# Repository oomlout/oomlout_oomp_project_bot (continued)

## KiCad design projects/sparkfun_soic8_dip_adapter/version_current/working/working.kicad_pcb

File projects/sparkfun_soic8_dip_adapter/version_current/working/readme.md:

# SOIC8-DIP_Adapter by sparkfun  
This is a harvested standardized copy of a project from github.  
The original project can be found at:  
https://github.com/sparkfun/SOIC8-DIP_Adapter  
Please consult that link for additional, details, files, and license information.  
Note: It was auto harvested and if the original repo had more than one board file or anything out of the ordinary the files here are likely not representative.

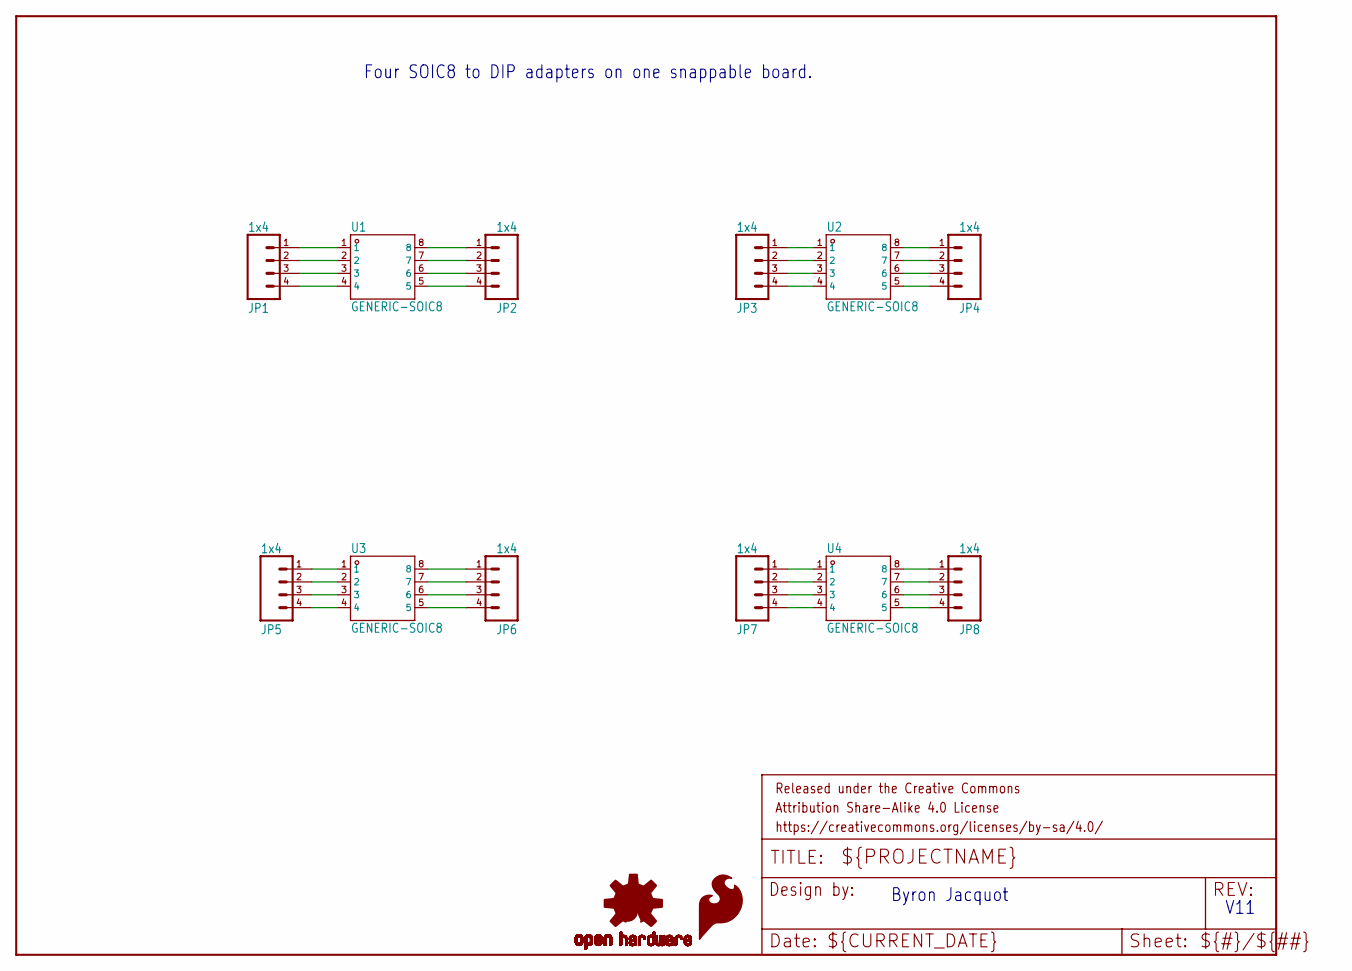
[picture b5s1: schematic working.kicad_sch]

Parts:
FRAME1: FRAME-LETTER; CREATIVE_COMMONS
JP1, JP3, JP5, JP7: 1x4; 1X04_NO_SILK
JP2, JP4, JP6, JP8: 1x4; 1X04_NO_SILK_ALL_ROUND
LOGO1: SFE_LOGO_FLAME.1_INCH; SFE_LOGO_FLAME_.1
LOGO2: OSHW-LOGOS; OSHW-LOGO-S
U1, U2, U3, U4: GENERIC-SOIC8; SO08-UNIVERSAL

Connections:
unnamed: JP1.1, U1.1
unnamed: JP1.2, U1.2
unnamed: JP1.3, U1.3
unnamed: JP1.4, U1.4
unnamed: JP2.1, U1.8
unnamed: JP2.2, U1.7
unnamed: JP2.3, U1.6
unnamed: JP2.4, U1.5
unnamed: JP3.1, U2.1
unnamed: JP3.2, U2.2
unnamed: JP3.3, U2.3
unnamed: JP3.4, U2.4
unnamed: JP4.1, U2.8
unnamed: JP4.2, U2.7
unnamed: JP4.3, U2.6
unnamed: JP4.4, U2.5
unnamed: JP5.1, U3.1
unnamed: JP5.2, U3.2
unnamed: JP5.3, U3.3
unnamed: JP5.4, U3.4
unnamed: JP6.4, U3.5
unnamed: JP6.3, U3.6
unnamed: JP6.2, U3.7
unnamed: JP6.1, U3.8
unnamed: JP7.1, U4.1
unnamed: JP7.2, U4.2
unnamed: JP7.3, U4.3
unnamed: JP7.4, U4.4
unnamed: JP8.1, U4.8
unnamed: JP8.2, U4.7
unnamed: JP8.3, U4.6
unnamed: JP8.4, U4.5

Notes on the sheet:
Four SOIC8 to DIP adapters on one snappable board.
V11
Byron Jacquot

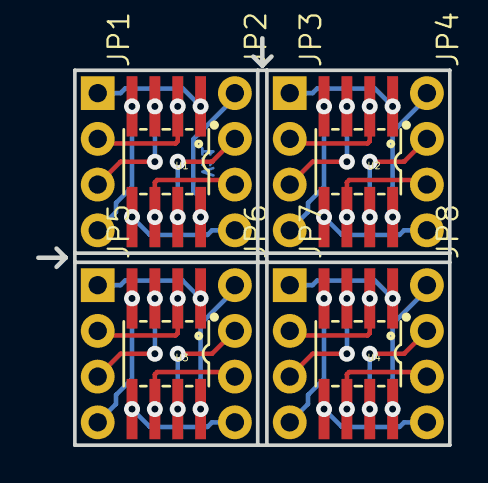
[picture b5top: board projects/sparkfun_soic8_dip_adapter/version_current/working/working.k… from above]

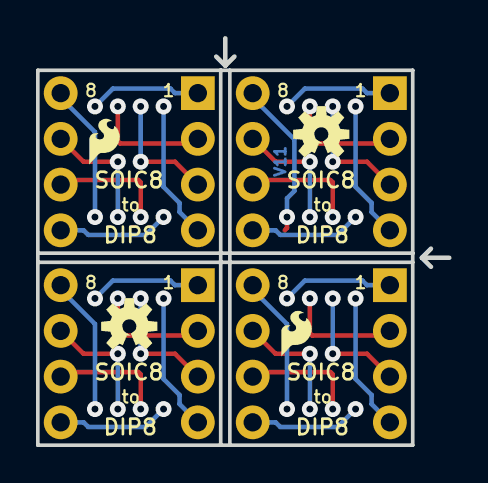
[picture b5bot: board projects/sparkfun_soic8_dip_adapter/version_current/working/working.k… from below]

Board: 2 copper layers, 22.9 x 22.6 mm, 17 parts (4 on the bottom side), 32 nets.

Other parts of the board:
LOGO3: OSHW-LOGOS; OSHW-LOGO-S
LOGO4: SFE_LOGO_FLAME.1_INCH; SFE_LOGO_FLAME_.1@1

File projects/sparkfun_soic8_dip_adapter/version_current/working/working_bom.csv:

"Id";"Designator";"Footprint";"Quantity";"Designation";"Supplier and ref";
1;"JP2,JP4,JP8,JP6";"1X04_NO_SILK_ALL_ROUND";4;"1x4";;;
2;"JP3,JP1,JP7,JP5";"1X04_NO_SILK";4;"1x4";;;
3;"U1,U3,U2,U4";"SO08-UNIVERSAL";4;"GENERIC-SOIC8";;;
4;"FRAME1";"CREATIVE_COMMONS";1;"frame";;;
5;"LOGO4";"SFE_LOGO_FLAME_.1@1";1;"SFE_LOGO_FLAME.1_INCH";;;
6;"LOGO1";"SFE_LOGO_FLAME_.1";1;"SFE_LOGO_FLAME.1_INCH";;;
7;"LOGO2,LOGO3";"OSHW-LOGO-S";2;"OSHW-LOGOS";;;

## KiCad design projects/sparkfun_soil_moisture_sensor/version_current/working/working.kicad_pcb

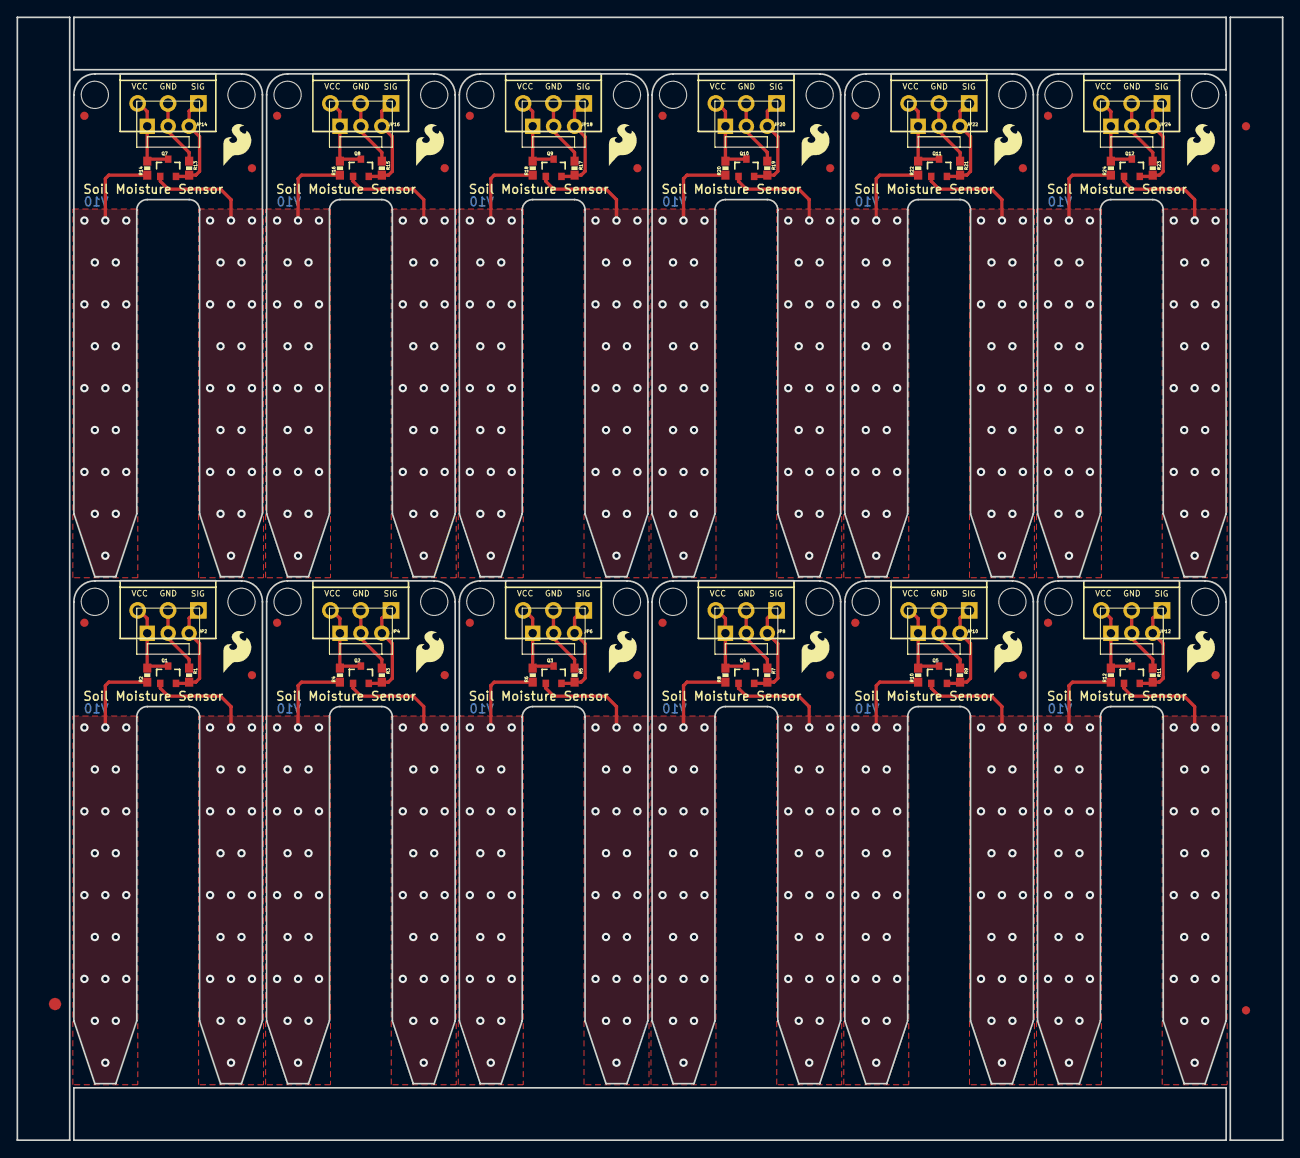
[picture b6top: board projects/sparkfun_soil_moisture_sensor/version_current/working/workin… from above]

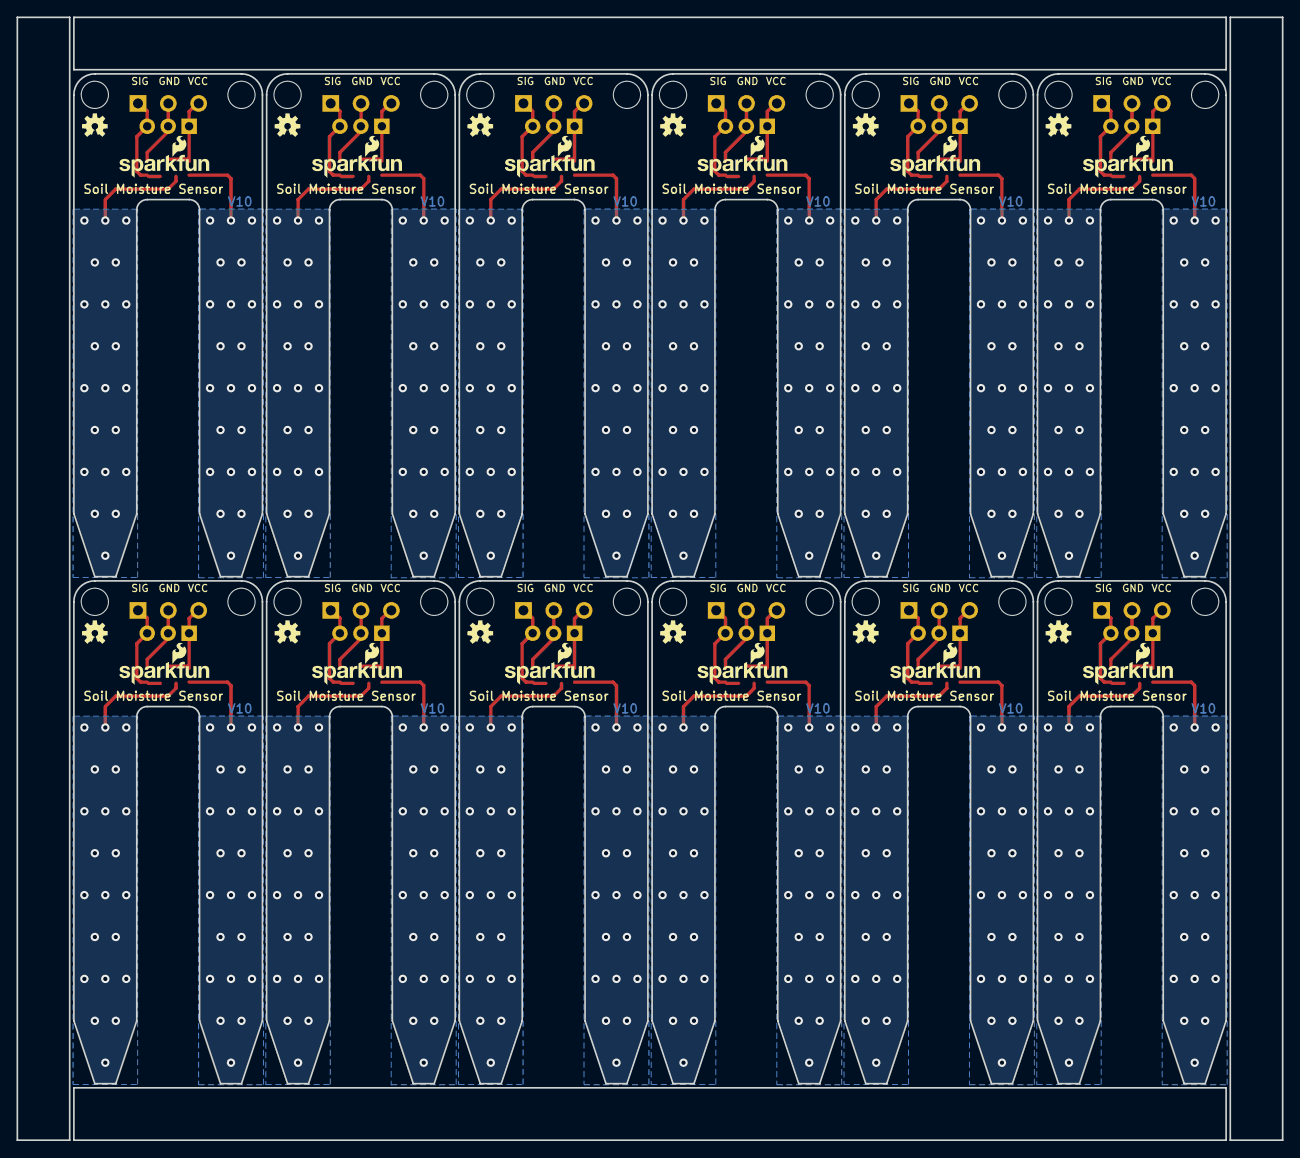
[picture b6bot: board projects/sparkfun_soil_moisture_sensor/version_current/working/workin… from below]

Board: 2 copper layers, 153.4 x 136.1 mm, 147 parts (24 on the bottom side), 36 nets.

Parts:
E$1: FIDUCIAL-1.5X3
E$4, E$5: FIDUCIAL-1X2
FID1, FID2, FID3, FID4, FID5, FID6, FID7, FID8, FID9, FID10, FID11, FID12, FID13, FID14, FID15, FID16, FID17, FID18, FID19, FID20, FID21, FID22, FID23, FID24: FIDUCIAL1X2; FIDUCIAL-1X2
JP1, JP3, JP5, JP7, JP9, JP11, JP13, JP15, JP17, JP19, JP21, JP23: DNP; MOLEX-1X3
JP2, JP4, JP6, JP8, JP10, JP12, JP14, JP16, JP18, JP20, JP22, JP24: SCREWTERMINAL-3.5MM-3_LOCK.007S
LOGO1, LOGO3, LOGO5, LOGO7, LOGO9, LOGO11, LOGO13, LOGO15, LOGO17, LOGO19, LOGO21, LOGO23: SFE_LOGO_NAME_FLAME.1_INCH; SFE_LOGO_NAME_FLAME_.1
LOGO2, LOGO4, LOGO6, LOGO8, LOGO10, LOGO12, LOGO14, LOGO16, LOGO18, LOGO20, LOGO22, LOGO24: OSHW-LOGOS; OSHW-LOGO-S
Q1, Q2, Q3, Q4, Q5, Q6, Q7, Q8, Q9, Q10, Q11, Q12: 2N3904; SOT23-3
R1, R3, R5, R7, R9, R11, R13, R15, R17, R19, R21, R23: 10k; 0603-RES
R2, R4, R6, R8, R10, R12, R14, R16, R18, R20, R22, R24: 100; 0603-RES
STANDOFF1, STANDOFF2, STANDOFF3, STANDOFF4, STANDOFF5, STANDOFF6, STANDOFF7, STANDOFF8, STANDOFF9, STANDOFF10, STANDOFF11, STANDOFF12, STANDOFF13, STANDOFF14, STANDOFF15, STANDOFF16, STANDOFF17, STANDOFF18, STANDOFF19, STANDOFF20, STANDOFF21, STANDOFF22, STANDOFF23, STANDOFF24: STAND-OFF
U$1, U$2, U$3, U$4, U$5, U$6, U$7, U$8, U$9, U$10, U$11, U$12: SFE_LOGO_FLAME_.2

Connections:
GND: JP1.2, JP2.2, R1.1
GND1: JP3.2, JP4.2, R3.1
GND2: JP5.2, JP6.2, R5.1
GND3: JP7.2, JP8.2, R7.1
GND4: JP9.2, JP10.2, R9.1
GND5: JP11.2, JP12.2, R11.1
GND6: JP13.2, JP14.2, R13.1
GND7: JP15.2, JP16.2, R15.1
GND8: JP17.2, JP18.2, R17.1
GND9: JP19.2, JP20.2, R19.1
GND10: JP21.2, JP22.2, R21.1
GND11: JP23.2, JP24.2, R23.1
SIG: JP1.3, JP2.1, Q1.2, R1.2
SIG1: JP3.3, JP4.1, Q2.2, R3.2
SIG2: JP5.3, JP6.1, Q3.2, R5.2
SIG3: JP7.3, JP8.1, Q4.2, R7.2
SIG4: JP9.3, JP10.1, Q5.2, R9.2
SIG5: JP11.3, JP12.1, Q6.2, R11.2
SIG6: JP13.3, JP14.1, Q7.2, R13.2
SIG7: JP15.3, JP16.1, Q8.2, R15.2
SIG8: JP17.3, JP18.1, Q9.2, R17.2
SIG9: JP19.3, JP20.1, Q10.2, R19.2
SIG10: JP21.3, JP22.1, Q11.2, R21.2
SIG11: JP23.3, JP24.1, Q12.2, R23.2
VCC: JP1.1, JP2.3, Q1.3, R2.2
VCC1: JP3.1, JP4.3, Q2.3, R4.2
VCC2: JP5.1, JP6.3, Q3.3, R6.2
VCC3: JP7.1, JP8.3, Q4.3, R8.2
VCC4: JP9.1, JP10.3, Q5.3, R10.2
VCC5: JP11.1, JP12.3, Q6.3, R12.2
VCC6: JP13.1, JP14.3, Q7.3, R14.2
VCC7: JP15.1, JP16.3, Q8.3, R16.2
VCC8: JP17.1, JP18.3, Q9.3, R18.2
VCC9: JP19.1, JP20.3, Q10.3, R20.2
VCC10: JP21.1, JP22.3, Q11.3, R22.2
VCC11: JP23.1, JP24.3, Q12.3, R24.2

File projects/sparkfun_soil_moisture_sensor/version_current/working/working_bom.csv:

"Id";"Designator";"Footprint";"Quantity";"Designation";"Supplier and ref";
1;"STANDOFF23,STANDOFF10,STANDOFF18,STANDOFF5,STANDOFF12,STANDOFF20,STANDOFF4,STANDOFF8,STANDOFF2,STANDOFF6,STANDOFF7,STANDOFF1,STANDOFF21,STANDOFF16,STANDOFF11,STANDOFF13,STANDOFF19,STANDOFF17,STANDOFF15,STANDOFF14,STANDOFF3,STANDOFF9,STANDOFF24,STANDOFF22";"STAND-OFF";24;"STAND-OFF";;;
2;"JP8,JP22,JP12,JP20,JP2,JP6,JP14,JP4,JP10,JP24,JP16,JP18";"SCREWTERMINAL-3.5MM-3_LOCK.007S";12;"";;;
3;"R3,R23,R9,R7,R11,R19,R21,R17,R1,R5,R13,R15";"0603-RES";12;"10k";;;
4;"FID22,FID23,FID14,FID18,FID3,FID5,FID12,FID2,FID20,FID8,FID11,FID16,FID9,FID6,FID1,FID17,FID7,FID15,FID24,FID21,FID19,FID10,FID13,FID4";"FIDUCIAL-1X2";24;"FIDUCIAL1X2";;;
5;"R12,R6,R2,R22,R4,R8,R10,R24,R14,R16,R20,R18";"0603-RES";12;"100";;;
6;"U$9,U$5,U$7,U$1,U$10,U$2,U$8,U$3,U$12,U$11,U$4,U$6";"SFE_LOGO_FLAME_.2";12;"";;;
7;"Q10,Q8,Q6,Q9,Q4,Q2,Q12,Q11,Q7,Q1,Q3,Q5";"SOT23-3";12;"2N3904";;;
8;"JP19,JP3,JP17,JP7,JP13,JP21,JP11,JP5,JP1,JP9,JP23,JP15";"MOLEX-1X3";12;"DNP";;;
9;"E$1";"FIDUCIAL-1.5X3";1;"";;;
10;"E$5,E$4";"FIDUCIAL-1X2";2;"";;;
11;"LOGO1,LOGO15,LOGO13,LOGO3,LOGO5,LOGO9,LOGO7,LOGO17,LOGO11,LOGO21,LOGO23,LOGO19";"SFE_LOGO_NAME_FLAME_.1";12;"SFE_LOGO_NAME_FLAME.1_INCH";;;
12;"LOGO22,LOGO12,LOGO6,LOGO2,LOGO10,LOGO20,LOGO4,LOGO8,LOGO24,LOGO18,LOGO14,LOGO16";"OSHW-LOGO-S";12;"OSHW-LOGOS";;;

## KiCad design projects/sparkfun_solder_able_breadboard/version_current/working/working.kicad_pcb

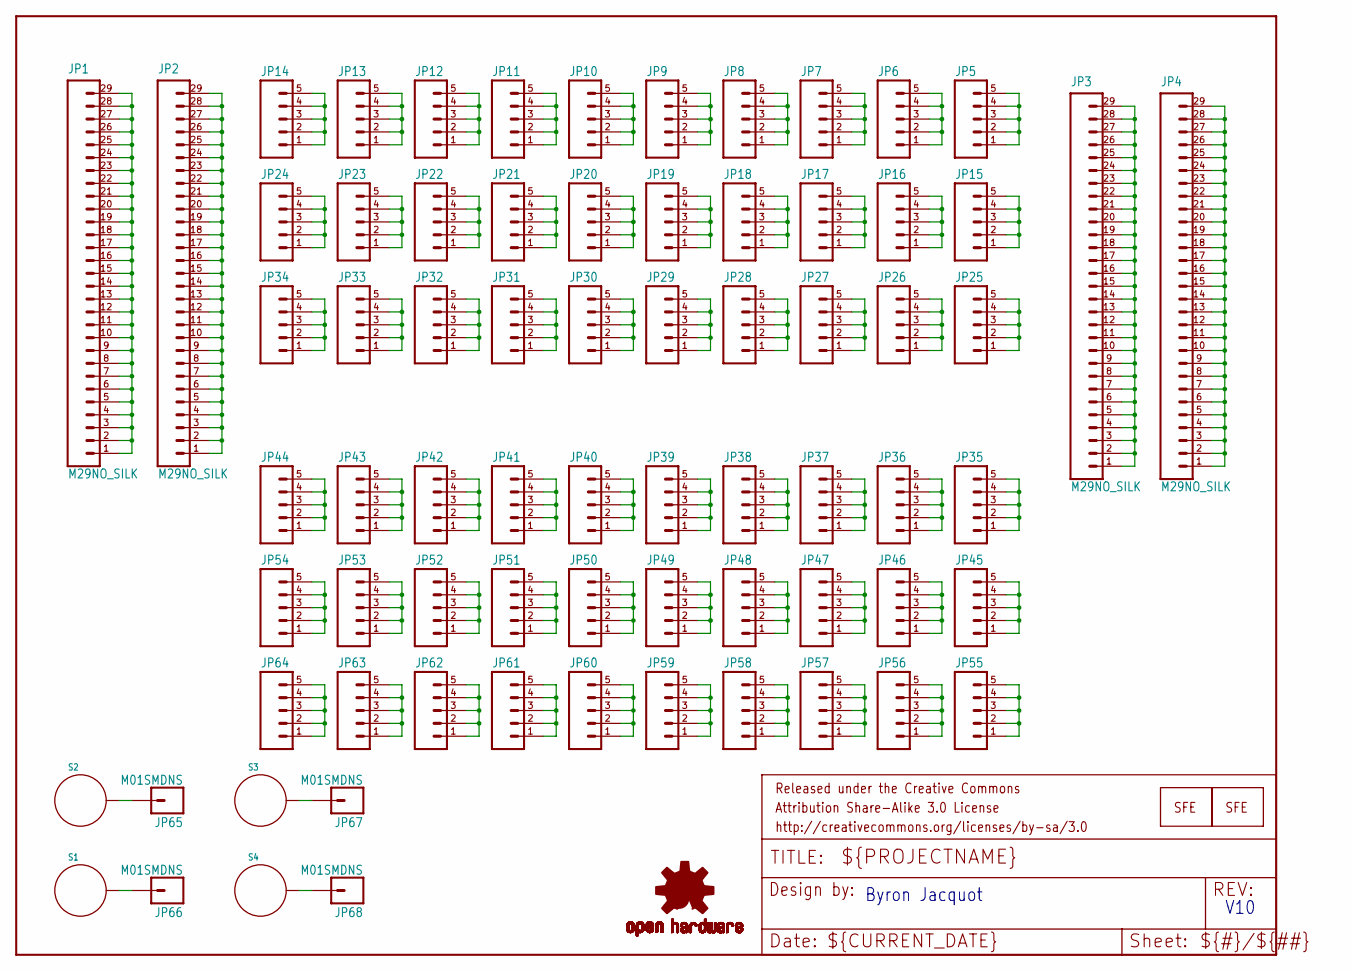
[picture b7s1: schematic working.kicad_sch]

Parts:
FRAME1: FRAME-LETTER; CREATIVE_COMMONS
JP1, JP2, JP3, JP4: M29NO_SILK; 1X29_NO_SILK
JP5, JP6, JP7, JP8, JP9, JP10, JP11, JP12, JP13, JP14, JP15, JP16, JP17, JP18, JP19, JP20, JP21, JP22, JP23, JP24, JP25, JP26, JP27, JP28, JP29, JP30, JP31, JP32, JP33, JP34, JP35, JP36, JP37, JP38, JP39, JP40, JP41, JP42, JP43, JP44, JP45, JP46, JP47, JP48, JP49, JP50, JP51, JP52, JP53, JP54, JP55, JP56, JP57, JP58, JP59, JP60, JP61, JP62, JP63, JP64: M05NO_SILK; 1X05_NO_SILK
JP65, JP66, JP67, JP68: M01SMDNS; 1X01NS
LOGO1: LOGO-SFECP; SFE-LOGO-FLAME-COPPER
LOGO2: LOGO-SFENEW; SFE-NEW-WEBLOGO
LOGO3: OSHW-LOGOS; OSHW-LOGO-S
S1, S2, S3, S4: STANDOFF_ELECTRICAL; STANDOFF-ELECTRICAL

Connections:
unnamed: JP1.1, JP1.2, JP1.3, JP1.4, JP1.5, JP1.6, JP1.7, JP1.8, JP1.9, JP1.10, JP1.11, JP1.12, JP1.13, JP1.14, JP1.15, JP1.16, JP1.17, JP1.18, JP1.19, JP1.20, JP1.21, JP1.22, JP1.23, JP1.24, JP1.25, JP1.26, JP1.27, JP1.28, JP1.29
unnamed: JP2.1, JP2.2, JP2.3, JP2.4, JP2.5, JP2.6, JP2.7, JP2.8, JP2.9, JP2.10, JP2.11, JP2.12, JP2.13, JP2.14, JP2.15, JP2.16, JP2.17, JP2.18, JP2.19, JP2.20, JP2.21, JP2.22, JP2.23, JP2.24, JP2.25, JP2.26, JP2.27, JP2.28, JP2.29
unnamed: JP3.1, JP3.2, JP3.3, JP3.4, JP3.5, JP3.6, JP3.7, JP3.8, JP3.9, JP3.10, JP3.11, JP3.12, JP3.13, JP3.14, JP3.15, JP3.16, JP3.17, JP3.18, JP3.19, JP3.20, JP3.21, JP3.22, JP3.23, JP3.24, JP3.25, JP3.26, JP3.27, JP3.28, JP3.29
unnamed: JP4.1, JP4.2, JP4.3, JP4.4, JP4.5, JP4.6, JP4.7, JP4.8, JP4.9, JP4.10, JP4.11, JP4.12, JP4.13, JP4.14, JP4.15, JP4.16, JP4.17, JP4.18, JP4.19, JP4.20, JP4.21, JP4.22, JP4.23, JP4.24, JP4.25, JP4.26, JP4.27, JP4.28, JP4.29
unnamed: JP10.1, JP10.2, JP10.3, JP10.4, JP10.5
unnamed: JP5.1, JP5.2, JP5.3, JP5.4, JP5.5
unnamed: JP6.1, JP6.2, JP6.3, JP6.4, JP6.5
unnamed: JP7.1, JP7.2, JP7.3, JP7.4, JP7.5
unnamed: JP8.1, JP8.2, JP8.3, JP8.4, JP8.5
unnamed: JP9.1, JP9.2, JP9.3, JP9.4, JP9.5
unnamed: JP11.1, JP11.2, JP11.3, JP11.4, JP11.5
unnamed: JP12.1, JP12.2, JP12.3, JP12.4, JP12.5
unnamed: JP13.1, JP13.2, JP13.3, JP13.4, JP13.5
unnamed: JP14.1, JP14.2, JP14.3, JP14.4, JP14.5
unnamed: JP15.1, JP15.2, JP15.3, JP15.4, JP15.5
unnamed: JP16.1, JP16.2, JP16.3, JP16.4, JP16.5
unnamed: JP17.1, JP17.2, JP17.3, JP17.4, JP17.5
unnamed: JP18.1, JP18.2, JP18.3, JP18.4, JP18.5
unnamed: JP19.1, JP19.2, JP19.3, JP19.4, JP19.5
unnamed: JP20.1, JP20.2, JP20.3, JP20.4, JP20.5
unnamed: JP21.1, JP21.2, JP21.3, JP21.4, JP21.5
unnamed: JP22.1, JP22.2, JP22.3, JP22.4, JP22.5
unnamed: JP23.1, JP23.2, JP23.3, JP23.4, JP23.5
unnamed: JP24.1, JP24.2, JP24.3, JP24.4, JP24.5
unnamed: JP25.1, JP25.2, JP25.3, JP25.4, JP25.5
unnamed: JP26.1, JP26.2, JP26.3, JP26.4, JP26.5
unnamed: JP27.1, JP27.2, JP27.3, JP27.4, JP27.5
unnamed: JP28.1, JP28.2, JP28.3, JP28.4, JP28.5
unnamed: JP29.1, JP29.2, JP29.3, JP29.4, JP29.5
unnamed: JP30.1, JP30.2, JP30.3, JP30.4, JP30.5
unnamed: JP31.1, JP31.2, JP31.3, JP31.4, JP31.5
unnamed: JP32.1, JP32.2, JP32.3, JP32.4, JP32.5
unnamed: JP33.1, JP33.2, JP33.3, JP33.4, JP33.5
unnamed: JP34.1, JP34.2, JP34.3, JP34.4, JP34.5
unnamed: JP35.1, JP35.2, JP35.3, JP35.4, JP35.5
unnamed: JP36.1, JP36.2, JP36.3, JP36.4, JP36.5
unnamed: JP37.1, JP37.2, JP37.3, JP37.4, JP37.5
unnamed: JP38.1, JP38.2, JP38.3, JP38.4, JP38.5
unnamed: JP39.1, JP39.2, JP39.3, JP39.4, JP39.5
unnamed: JP40.1, JP40.2, JP40.3, JP40.4, JP40.5
unnamed: JP41.1, JP41.2, JP41.3, JP41.4, JP41.5
unnamed: JP42.1, JP42.2, JP42.3, JP42.4, JP42.5
unnamed: JP43.1, JP43.2, JP43.3, JP43.4, JP43.5
unnamed: JP44.1, JP44.2, JP44.3, JP44.4, JP44.5
unnamed: JP45.1, JP45.2, JP45.3, JP45.4, JP45.5
unnamed: JP46.1, JP46.2, JP46.3, JP46.4, JP46.5
unnamed: JP47.1, JP47.2, JP47.3, JP47.4, JP47.5
unnamed: JP48.1, JP48.2, JP48.3, JP48.4, JP48.5
unnamed: JP49.1, JP49.2, JP49.3, JP49.4, JP49.5
unnamed: JP50.1, JP50.2, JP50.3, JP50.4, JP50.5
unnamed: JP51.1, JP51.2, JP51.3, JP51.4, JP51.5
unnamed: JP52.1, JP52.2, JP52.3, JP52.4, JP52.5
unnamed: JP53.1, JP53.2, JP53.3, JP53.4, JP53.5
unnamed: JP54.1, JP54.2, JP54.3, JP54.4, JP54.5
unnamed: JP55.1, JP55.2, JP55.3, JP55.4, JP55.5
unnamed: JP56.1, JP56.2, JP56.3, JP56.4, JP56.5
unnamed: JP57.1, JP57.2, JP57.3, JP57.4, JP57.5
unnamed: JP58.1, JP58.2, JP58.3, JP58.4, JP58.5
unnamed: JP59.1, JP59.2, JP59.3, JP59.4, JP59.5
unnamed: JP60.1, JP60.2, JP60.3, JP60.4, JP60.5
unnamed: JP61.1, JP61.2, JP61.3, JP61.4, JP61.5
unnamed: JP62.1, JP62.2, JP62.3, JP62.4, JP62.5
unnamed: JP63.1, JP63.2, JP63.3, JP63.4, JP63.5
unnamed: JP64.1, JP64.2, JP64.3, JP64.4, JP64.5
unnamed: JP65.1, S2.P1
unnamed: JP66.1, S1.P1
unnamed: JP67.1, S3.P1
unnamed: JP68.1, S4.P1

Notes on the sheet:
Byron Jacquot
V10

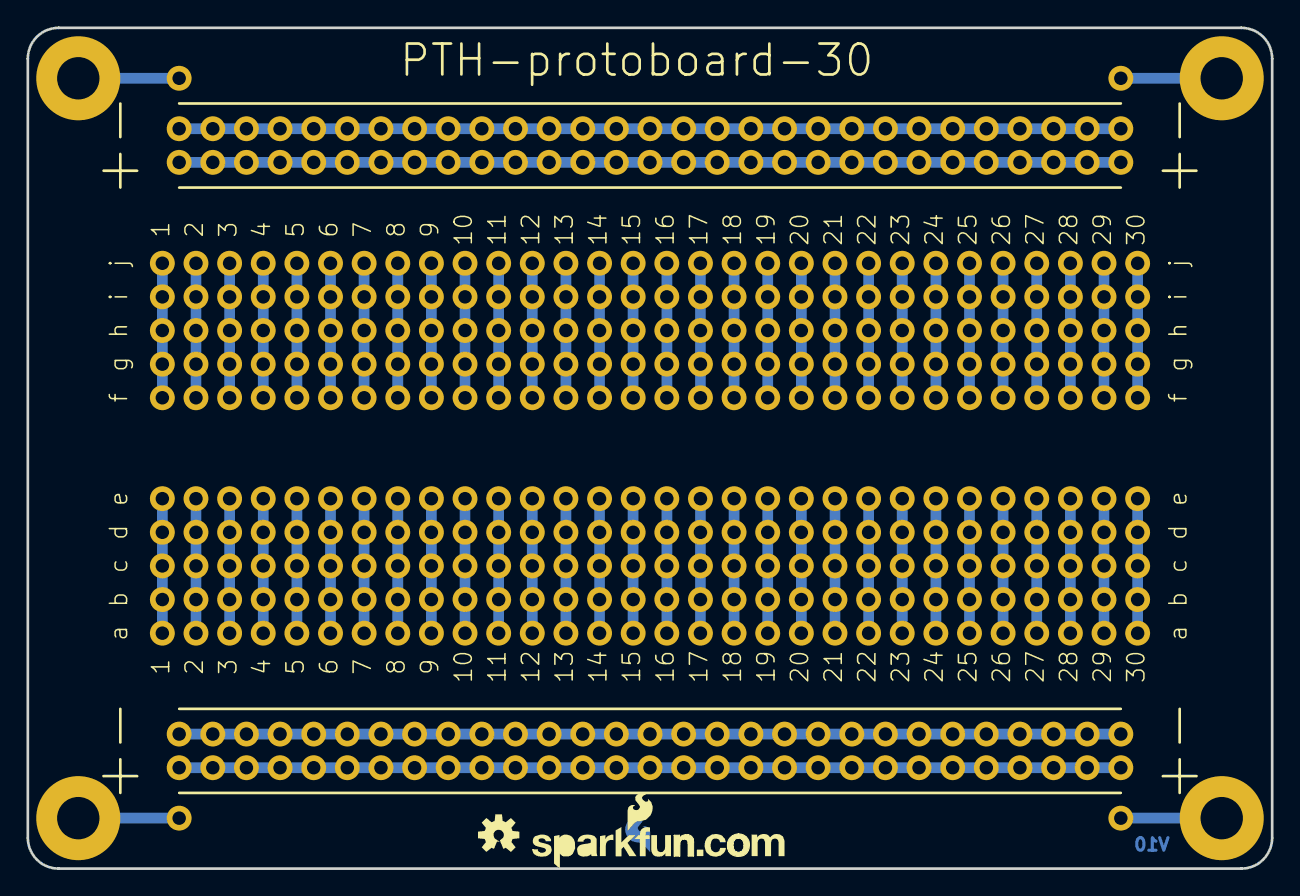
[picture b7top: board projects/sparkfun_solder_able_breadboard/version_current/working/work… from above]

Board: 2 copper layers, 94.0 x 63.5 mm, 76 parts (1 on the bottom side), 68 nets.

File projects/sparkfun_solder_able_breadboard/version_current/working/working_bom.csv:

"Id";"Designator";"Footprint";"Quantity";"Designation";"Supplier and ref";
1;"FRAME1";"CREATIVE_COMMONS";1;"FRAME-LETTER";;;
2;"JP3,JP2,JP1,JP4";"1X29_NO_SILK";4;"M29NO_SILK";;;
3;"JP43,JP42,JP48,JP9,JP34,JP60,JP26,JP27,JP20,JP21,JP51,JP47,JP25,JP61,JP29,JP63,JP18,JP39,JP19,JP49,JP28,JP45,JP32,JP46,JP38,JP14,JP40,JP7,JP50,JP53,JP15,JP23,JP22,JP58,JP41,JP64,JP13,JP56,JP16,JP11,JP12,JP10,JP55,JP52,JP54,JP8,JP36,JP24,JP59,JP57,JP30,JP62,JP31,JP37,JP17,JP5,JP44,JP35,JP6,JP33";"1X05_NO_SILK";60;"";;;
4;"JP66,JP67,JP65,JP68";"1X01NS";4;"M01SMDNS";;;
5;"LOGO2";"SFE-NEW-WEBLOGO";1;"LOGO-SFENEW";;;
6;"S3,S4,S1,S2";"STANDOFF-ELECTRICAL";4;"STANDOFF_ELECTRICAL";;;
7;"LOGO3";"OSHW-LOGO-S";1;"OSHW-LOGOS";;;
8;"LOGO1";"SFE-LOGO-FLAME-COPPER";1;"LOGO-SFECP";;;
